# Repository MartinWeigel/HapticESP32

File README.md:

# HapticESP32

This PCB provides a maximum of eight ERM/LRA drivers and two transistors to control binary actuators.
All haptic actuators can be controlled through an [Adafruit Feather HUZZAH32](https://www.adafruit.com/product/3405) microcontroller.

All SMDs are on one-side of the PCB only to reduce costs for the assembly service.

This board was designed using [KiCad 6.0](http://www.kicad.org).

## Design

## Parts
The part list is divided into two sections, the first one contains the parts if you decide to only solder the through-hole components yourself. The second BOM contains the SMD components.

### Through-hole components
Part                   | Quantity | Description
-----------------------|----------|-----------------------
Feather HUZZAH32       | 1        | ESP32 Microcontroller
Phoenix MPT-0,5-2-2.54 | 10       | 2-pin Terminalblock

### SMD components
Part               | Quantity | Description
-------------------|----------|-----------------
TCA9548APWR        | 1        | I2C Multiplexer
DRV2605LDGSR       | 8        | ERM/LRA Driver
MMBT5550LT1G       | 2        | NPN Transistor
Resistor 0402 1k   | 2        | Generic Resistor
Resistor 0402 4.7k | 27       | Generic Resistor
Capacitor 0402 1uF | 8        | Generic Capacitor

## License
<br />This work is licensed under a <a rel="license" href="http://creativecommons.org/licenses/by/4.0/">Creative Commons Attribution 4.0 International License</a>.

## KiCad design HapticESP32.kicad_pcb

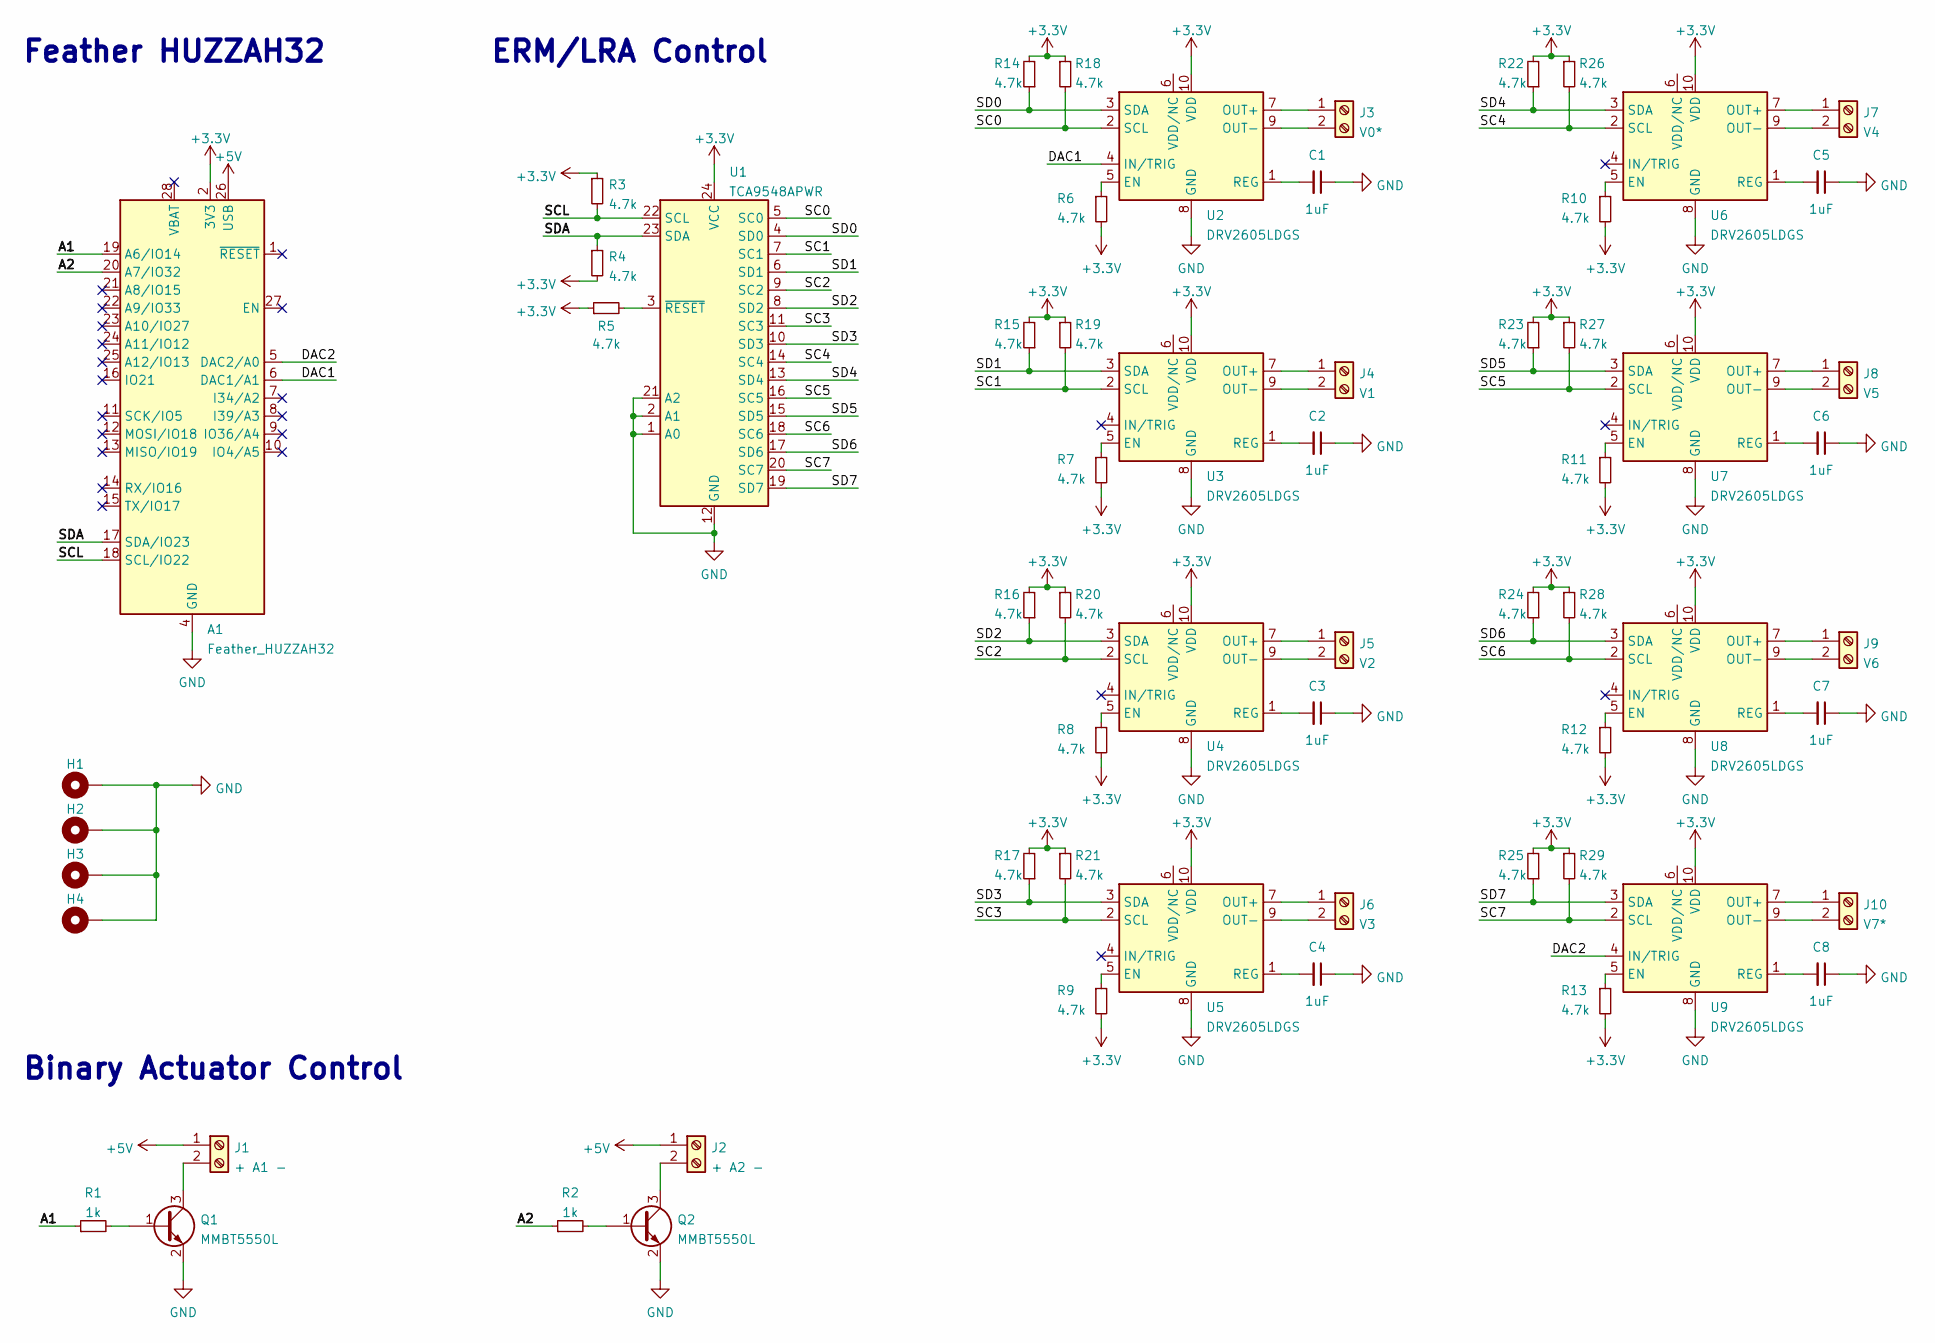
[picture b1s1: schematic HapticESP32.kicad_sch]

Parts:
A1: Feather_HUZZAH32; Adafruit_Feather
C1, C2, C3, C4, C5, C6, C7, C8: 1uF; C_0402_1005Metric
H1, H2, H3, H4: MountingHole_Pad; MountingHole_2.2mm_M2_DIN965_Pad
J1: + A1 -; TerminalBlock_Phoenix_MPT-0,5-2-2.54_1x02_P2.54mm_Horizontal
J2: + A2 -; TerminalBlock_Phoenix_MPT-0,5-2-2.54_1x02_P2.54mm_Horizontal
J3: V0*; TerminalBlock_Phoenix_MPT-0,5-2-2.54_1x02_P2.54mm_Horizontal
J4: V1; TerminalBlock_Phoenix_MPT-0,5-2-2.54_1x02_P2.54mm_Horizontal
J5: V2; TerminalBlock_Phoenix_MPT-0,5-2-2.54_1x02_P2.54mm_Horizontal
J6: V3; TerminalBlock_Phoenix_MPT-0,5-2-2.54_1x02_P2.54mm_Horizontal
J7: V4; TerminalBlock_Phoenix_MPT-0,5-2-2.54_1x02_P2.54mm_Horizontal
J8: V5; TerminalBlock_Phoenix_MPT-0,5-2-2.54_1x02_P2.54mm_Horizontal
J9: V6; TerminalBlock_Phoenix_MPT-0,5-2-2.54_1x02_P2.54mm_Horizontal
J10: V7*; TerminalBlock_Phoenix_MPT-0,5-2-2.54_1x02_P2.54mm_Horizontal
Q1, Q2: MMBT5550L; SOT-23
R1, R2: 1k; R_0402_1005Metric
R3, R4, R5, R6, R7, R8, R9, R10, R11, R12, R13, R14, R15, R16, R17, R18, R19, R20, R21, R22, R23, R24, R25, R26, R27, R28, R29: 4.7k; R_0402_1005Metric
U1: TCA9548APWR; TSSOP-24_4.4x7.8mm_P0.65mm
U2, U3, U4, U5, U6, U7, U8, U9: DRV2605LDGS; VSSOP-10_3x3mm_P0.5mm

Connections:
+3V3: A1.2 (3V3), R3.1, R4.2, R5.1, R6.2, R7.2, R8.2, R9.2, R10.2, R11.2, R12.2, R13.2, R14.2, R15.2, R16.2, R17.2, R18.1, R19.1, R20.1, R21.1, R22.2, R23.2, R24.2, R25.2, R26.1, R27.1, R28.1, R29.1, U1.24 (VCC), U2.10 (VDD), U3.10 (VDD), U4.10 (VDD), U5.10 (VDD), U6.10 (VDD), U7.10 (VDD), U8.10 (VDD), U9.10 (VDD)
+5V: A1.26 (USB), J1.1, J2.1
/A1: A1.19 (A6/IO14), R1.1
/A2: A1.20 (A7/IO32), R2.1
/DAC1: A1.6 (DAC1/A1), U2.4 (IN/TRIG)
/DAC2: A1.5 (DAC2/A0), U9.4 (IN/TRIG)
/SC0: R18.2, U1.5 (SC0), U2.2 (SCL)
/SC1: R19.2, U1.7 (SC1), U3.2 (SCL)
/SC2: R20.2, U1.9 (SC2), U4.2 (SCL)
/SC3: R21.2, U1.11 (SC3), U5.2 (SCL)
/SC4: R26.2, U1.14 (SC4), U6.2 (SCL)
/SC5: R27.2, U1.16 (SC5), U7.2 (SCL)
/SC6: R28.2, U1.18 (SC6), U8.2 (SCL)
/SC7: R29.2, U1.20 (SC7), U9.2 (SCL)
/SCL: A1.18 (SCL/IO22), R3.2, U1.22 (SCL)
/SD0: R14.1, U1.4 (SD0), U2.3 (SDA)
/SD1: R15.1, U1.6 (SD1), U3.3 (SDA)
/SD2: R16.1, U1.8 (SD2), U4.3 (SDA)
/SD3: R17.1, U1.10 (SD3), U5.3 (SDA)
/SD4: R22.1, U1.13 (SD4), U6.3 (SDA)
/SD5: R23.1, U1.15 (SD5), U7.3 (SDA)
/SD6: R24.1, U1.17 (SD6), U8.3 (SDA)
/SD7: R25.1, U1.19 (SD7), U9.3 (SDA)
/SDA: A1.17 (SDA/IO23), R4.1, U1.23 (SDA)
GND: A1.4 (GND), C1.1, C2.1, C3.1, C4.1, C5.1, C6.1, C7.1, C8.1, H1.1, H2.1, H3.1, H4.1, Q1.2 (E), Q2.2 (E), U1.1 (A0), U1.2 (A1), U1.12 (GND), U1.21 (A2), U2.8 (GND), U3.8 (GND), U4.8 (GND), U5.8 (GND), U6.8 (GND), U7.8 (GND), U8.8 (GND), U9.8 (GND)
unnamed: C1.2, U2.1 (REG)
unnamed: C2.2, U3.1 (REG)
unnamed: C3.2, U4.1 (REG)
unnamed: C4.2, U5.1 (REG)
unnamed: C5.2, U6.1 (REG)
unnamed: C6.2, U7.1 (REG)
unnamed: C7.2, U8.1 (REG)
unnamed: C8.2, U9.1 (REG)
unnamed: J1.2, Q1.3 (C)
unnamed: J2.2, Q2.3 (C)
unnamed: J3.1, U2.7 (OUT+)
unnamed: J3.2, U2.9 (OUT-)
unnamed: J4.1, U3.7 (OUT+)
unnamed: J4.2, U3.9 (OUT-)
unnamed: J5.1, U4.7 (OUT+)
unnamed: J5.2, U4.9 (OUT-)
unnamed: J6.1, U5.7 (OUT+)
unnamed: J6.2, U5.9 (OUT-)
unnamed: J7.1, U6.7 (OUT+)
unnamed: J7.2, U6.9 (OUT-)
unnamed: J8.1, U7.7 (OUT+)
unnamed: J8.2, U7.9 (OUT-)
unnamed: J9.1, U8.7 (OUT+)
unnamed: J9.2, U8.9 (OUT-)
unnamed: J10.1, U9.7 (OUT+)
unnamed: J10.2, U9.9 (OUT-)
unnamed: Q1.1 (B), R1.2
unnamed: Q2.1 (B), R2.2
unnamed: R5.2, U1.3 (~RESET)
unnamed: R6.1, U2.5 (EN)
unnamed: R7.1, U3.5 (EN)
unnamed: R8.1, U4.5 (EN)
unnamed: R9.1, U5.5 (EN)
unnamed: R10.1, U6.5 (EN)
unnamed: R11.1, U7.5 (EN)
unnamed: R12.1, U8.5 (EN)
unnamed: R13.1, U9.5 (EN)

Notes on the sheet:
ERM/LRA Control
Feather HUZZAH32
Binary Actuator Control

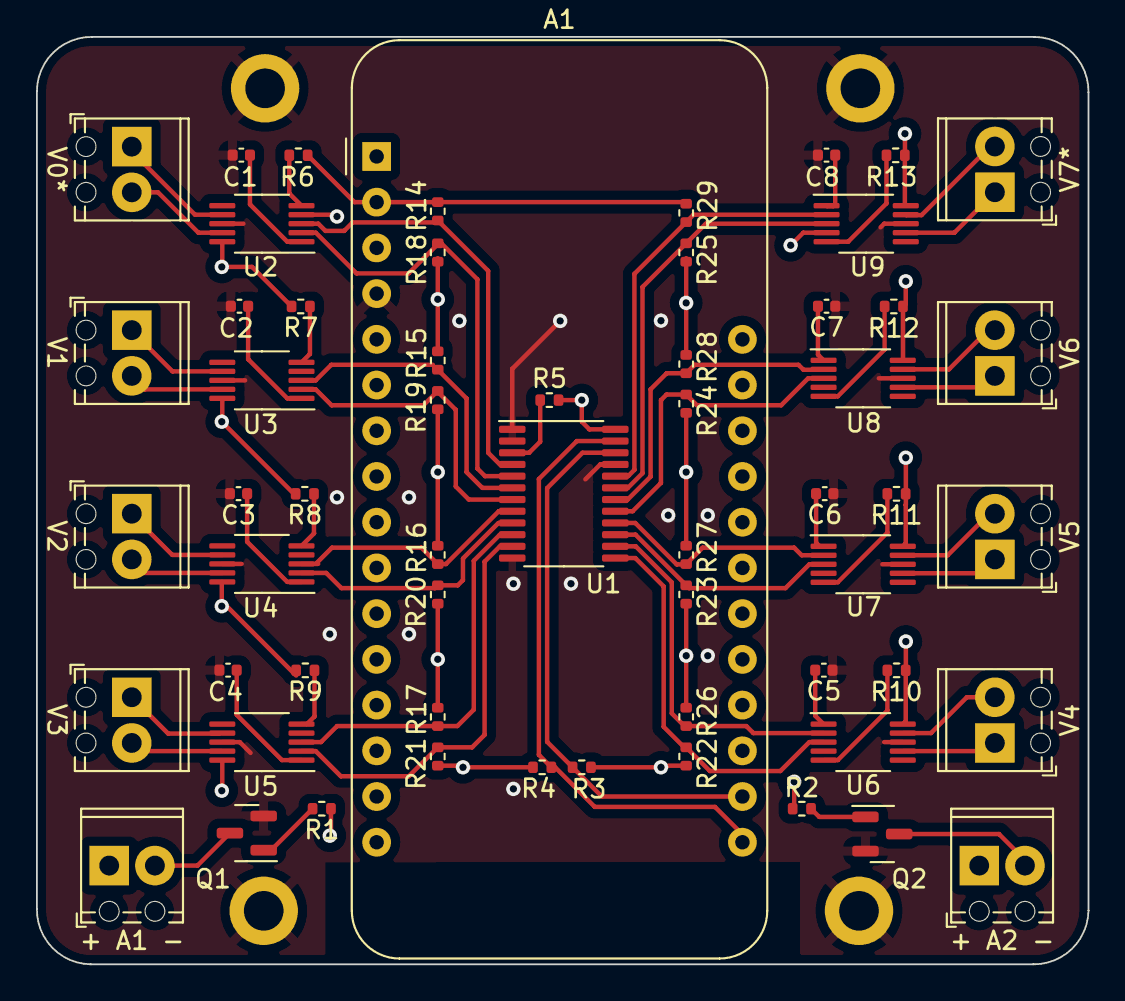
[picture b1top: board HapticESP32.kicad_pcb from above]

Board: 4 copper layers, 58.4 x 51.5 mm, 63 parts (0 on the bottom side), 62 nets.

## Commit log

2022-02-19 feat: first version of HapticESP32

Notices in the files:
HapticESP32.kicad_pcb:
License: CC BY 4.0
